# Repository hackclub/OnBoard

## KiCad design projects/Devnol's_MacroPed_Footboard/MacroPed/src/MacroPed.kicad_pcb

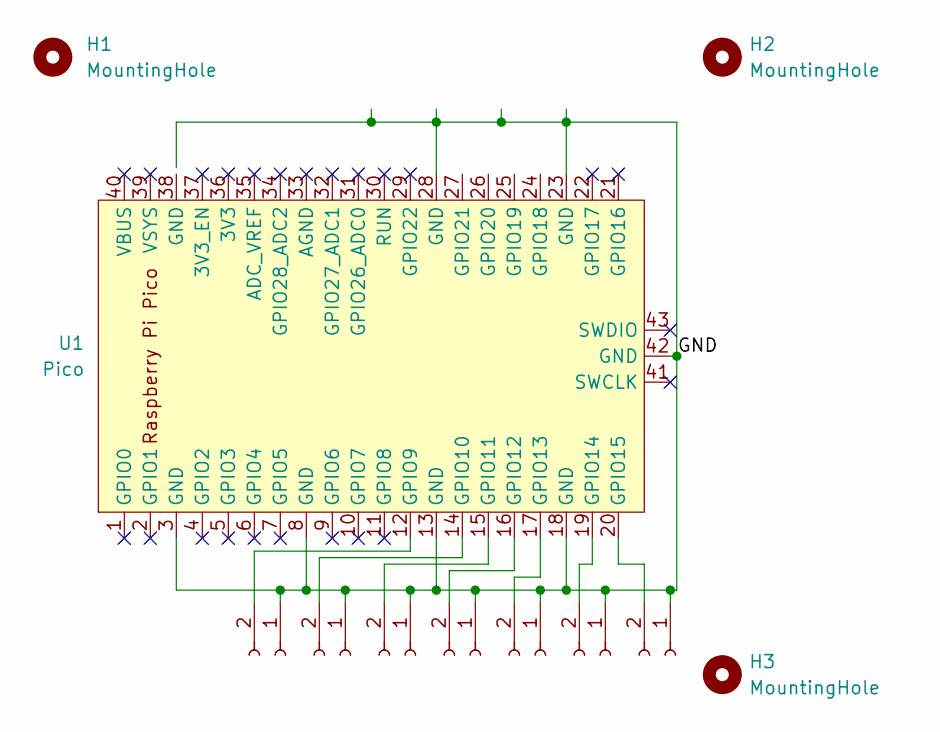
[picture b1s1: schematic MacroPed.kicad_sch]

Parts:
H1, H2, H3: MountingHole; MountingHole_2.7mm_M2.5_DIN965
J1, J2, J3, J4, J5, J6, J7: Conn_01x02_Socket; JST_PH_S2B-PH-K_1x02_P2.00mm_Horizontal
U1: Pico; RPi_Pico_SMD_TH

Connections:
/GND: J1.1, J2.1, J3.1, J4.1, J5.1, J6.1, J7.1, U1.3 (GND), U1.8 (GND), U1.13 (GND), U1.18 (GND), U1.23 (GND), U1.28 (GND), U1.42 (GND)
unnamed: J1.2, U1.12 (GPIO9)
unnamed: J2.2, U1.14 (GPIO10)
unnamed: J3.2, U1.15 (GPIO11)
unnamed: J4.2, U1.16 (GPIO12)
unnamed: J5.2, U1.17 (GPIO13)
unnamed: J6.2, U1.19 (GPIO14)
unnamed: J7.2, U1.20 (GPIO15)

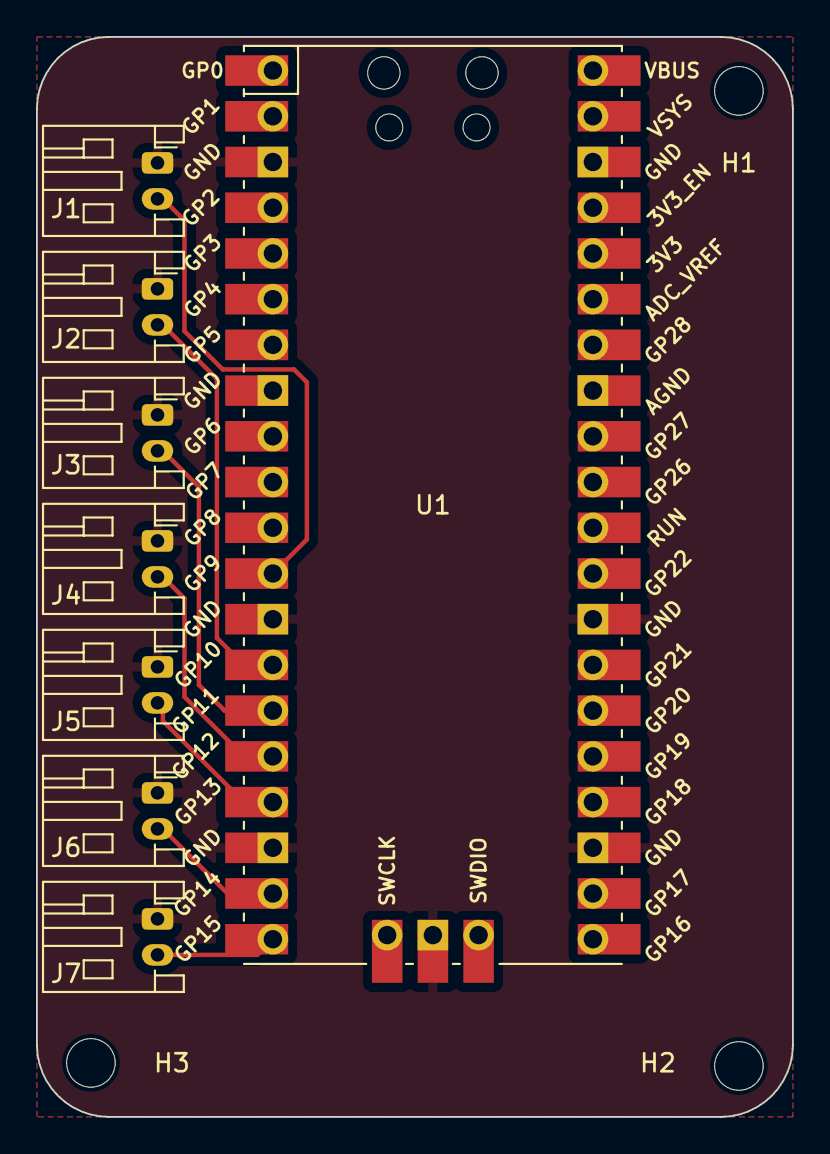
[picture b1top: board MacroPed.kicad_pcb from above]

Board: 2 copper layers, 42.0 x 60.0 mm, 11 parts (0 on the bottom side), 8 nets.

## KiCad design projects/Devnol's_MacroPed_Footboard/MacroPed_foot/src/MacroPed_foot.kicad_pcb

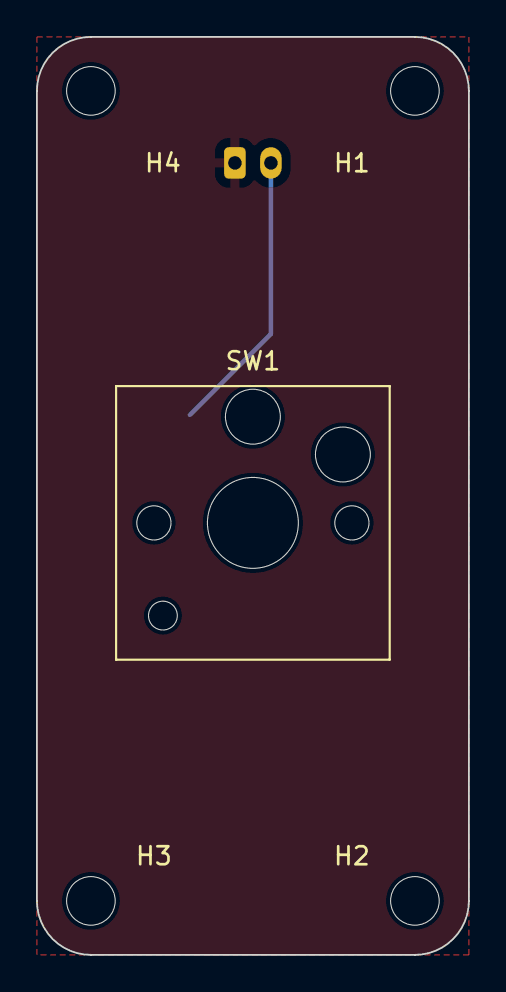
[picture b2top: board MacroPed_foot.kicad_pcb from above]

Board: 2 copper layers, 24.0 x 51.0 mm, 6 parts (1 on the bottom side), 2 nets.

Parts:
H1, H2, H3, H4: MountingHole; MountingHole_2.7mm_M2.5_DIN965
J1: Conn_01x02_Socket; JST_PH_S2B-PH-K_1x02_P2.00mm_Horizontal
SW1: SW_SPST; SW_Hotswap_Kailh_Choc_V1V2_2.00u_90deg

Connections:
/Foot_GND: J1.1, SW1.2 (B)
unnamed: J1.2, SW1.1 (A)

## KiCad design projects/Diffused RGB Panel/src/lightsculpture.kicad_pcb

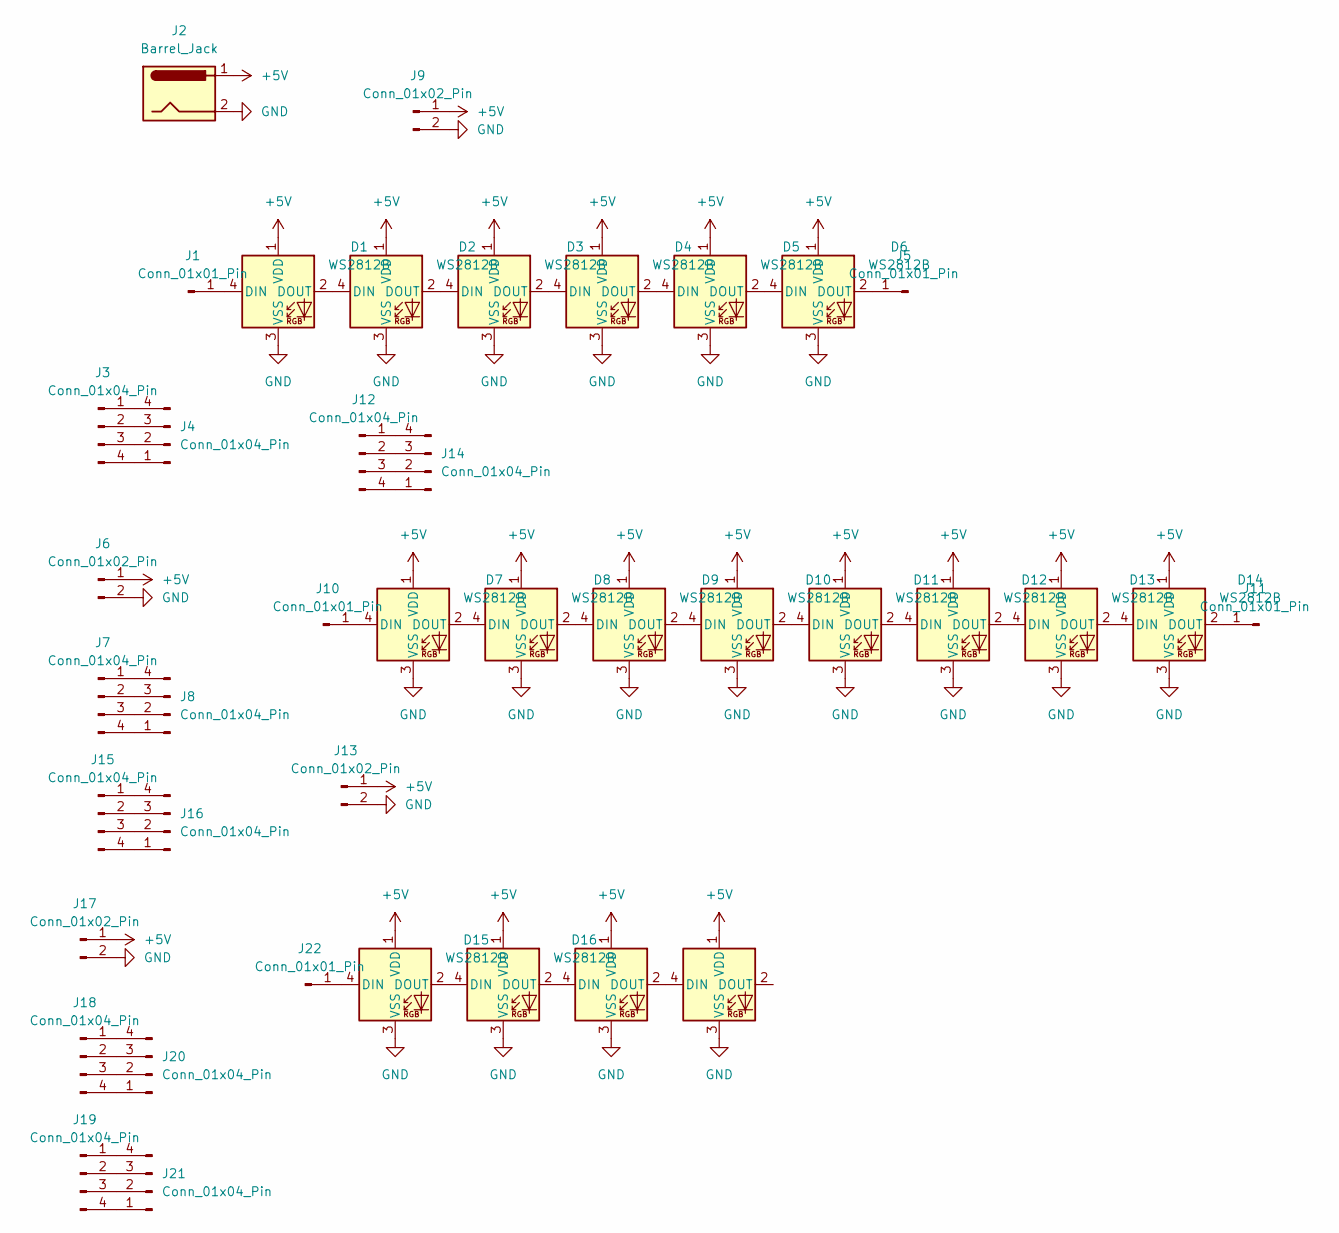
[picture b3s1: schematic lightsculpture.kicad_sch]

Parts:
D1, D2, D3, D4, D5, D6, D7, D8, D9, D10, D11, D12, D13, D14, D15, D16, D17, D18: WS2812B; LED_WS2812B_PLCC4_5.0x5.0mm_P3.2mm
J1, J5, J10, J11, J22: Conn_01x01_Pin; SolderWire-1.5sqmm_1x01_D1.7mm_OD3.9mm
J2: Barrel_Jack; SolderWire-1.5sqmm_1x02_P7.8mm_D1.7mm_OD3.9mm
J3, J4, J7, J8, J12, J14, J15, J16, J18, J19, J20, J21: Conn_01x04_Pin; SolderWire-1.5sqmm_1x04_P6mm_D1.7mm_OD3mm
J6, J9, J13, J17: Conn_01x02_Pin; SolderWire-1.5sqmm_1x02_P7.8mm_D1.7mm_OD3.9mm

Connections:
+5V: D1.1 (VDD), D2.1 (VDD), D3.1 (VDD), D4.1 (VDD), D5.1 (VDD), D6.1 (VDD), D7.1 (VDD), D8.1 (VDD), D9.1 (VDD), D10.1 (VDD), D11.1 (VDD), D12.1 (VDD), D13.1 (VDD), D14.1 (VDD), D15.1 (VDD), D16.1 (VDD), D17.1 (VDD), D18.1 (VDD), J2.1, J6.1, J9.1, J13.1, J17.1
GND: D1.3 (VSS), D2.3 (VSS), D3.3 (VSS), D4.3 (VSS), D5.3 (VSS), D6.3 (VSS), D7.3 (VSS), D8.3 (VSS), D9.3 (VSS), D10.3 (VSS), D11.3 (VSS), D12.3 (VSS), D13.3 (VSS), D14.3 (VSS), D15.3 (VSS), D16.3 (VSS), D17.3 (VSS), D18.3 (VSS), J2.2, J6.2, J9.2, J13.2, J17.2
unnamed: D1.4 (DIN), J1.1
unnamed: D1.2 (DOUT), D2.4 (DIN)
unnamed: D2.2 (DOUT), D3.4 (DIN)
unnamed: D3.2 (DOUT), D4.4 (DIN)
unnamed: D4.2 (DOUT), D5.4 (DIN)
unnamed: D5.2 (DOUT), D6.4 (DIN)
unnamed: D6.2 (DOUT), J5.1
unnamed: D7.4 (DIN), J10.1
unnamed: D7.2 (DOUT), D8.4 (DIN)
unnamed: D8.2 (DOUT), D9.4 (DIN)
unnamed: D9.2 (DOUT), D10.4 (DIN)
unnamed: D10.2 (DOUT), D11.4 (DIN)
unnamed: D11.2 (DOUT), D12.4 (DIN)
unnamed: D12.2 (DOUT), D13.4 (DIN)
unnamed: D13.2 (DOUT), D14.4 (DIN)
unnamed: D14.2 (DOUT), J11.1
unnamed: D15.4 (DIN), J22.1
unnamed: D15.2 (DOUT), D16.4 (DIN)
unnamed: D16.2 (DOUT), D17.4 (DIN)
unnamed: D17.2 (DOUT), D18.4 (DIN)
unnamed: J3.1, J4.4
unnamed: J3.2, J4.3
unnamed: J3.3, J4.2
unnamed: J3.4, J4.1
unnamed: J7.1, J8.4
unnamed: J7.2, J8.3
unnamed: J7.3, J8.2
unnamed: J7.4, J8.1
unnamed: J12.1, J14.4
unnamed: J12.2, J14.3
unnamed: J12.3, J14.2
unnamed: J12.4, J14.1
unnamed: J15.1, J16.4
unnamed: J15.2, J16.3
unnamed: J15.3, J16.2
unnamed: J15.4, J16.1
unnamed: J18.1, J20.4
unnamed: J18.2, J20.3
unnamed: J18.3, J20.2
unnamed: J18.4, J20.1
unnamed: J19.1, J21.4
unnamed: J19.2, J21.3
unnamed: J19.3, J21.2
unnamed: J19.4, J21.1

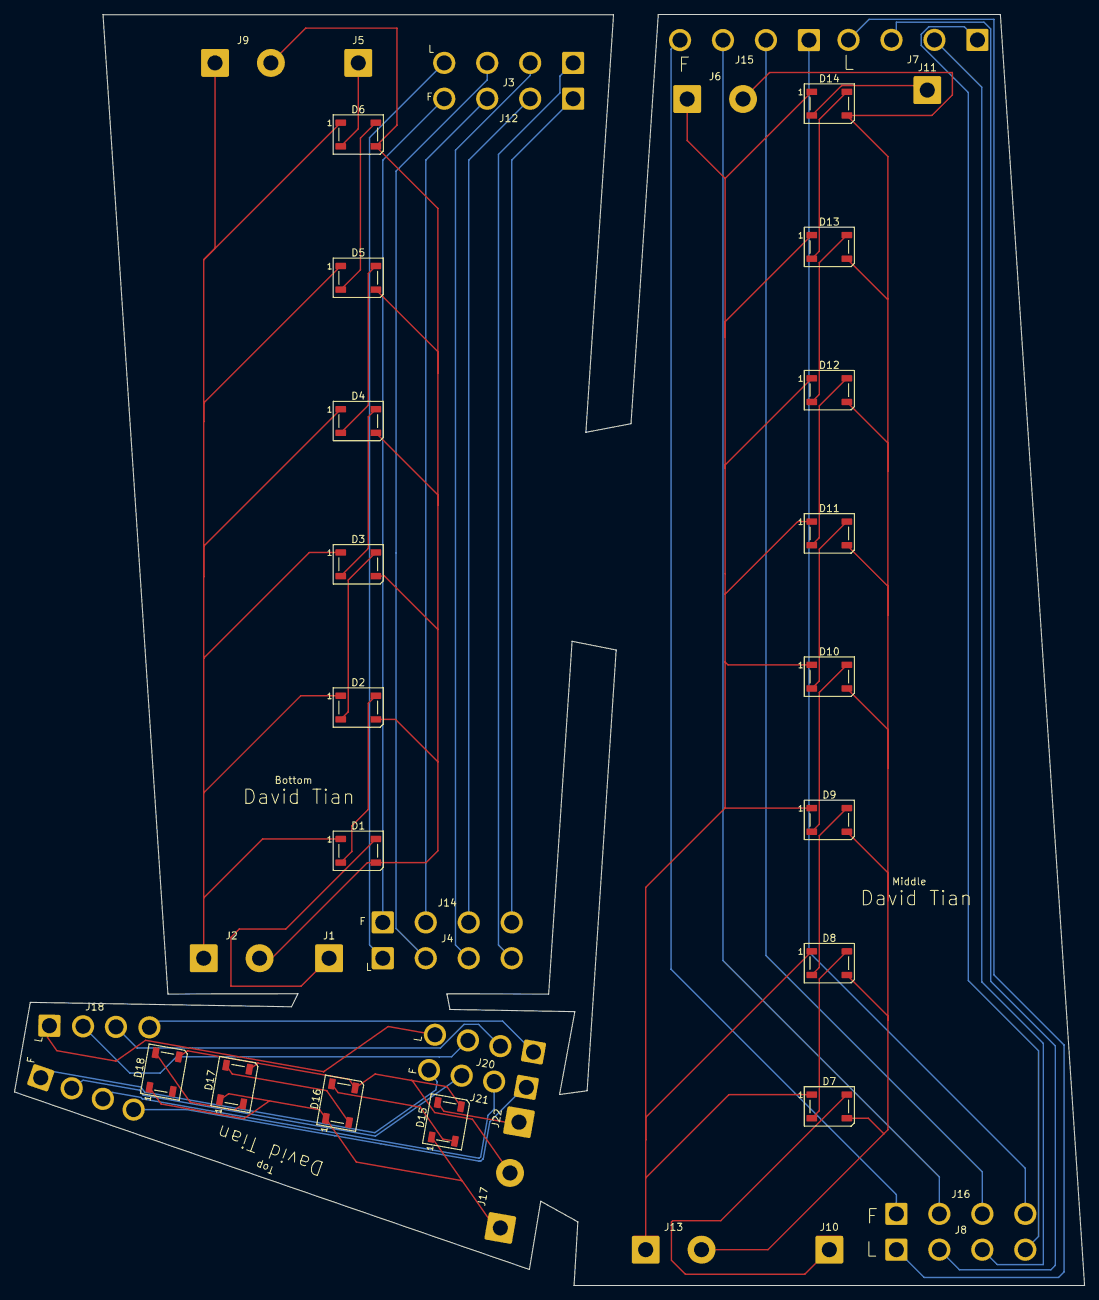
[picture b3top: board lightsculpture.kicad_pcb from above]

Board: 2 copper layers, 149.4 x 177.4 mm, 40 parts (1 on the bottom side), 46 nets.

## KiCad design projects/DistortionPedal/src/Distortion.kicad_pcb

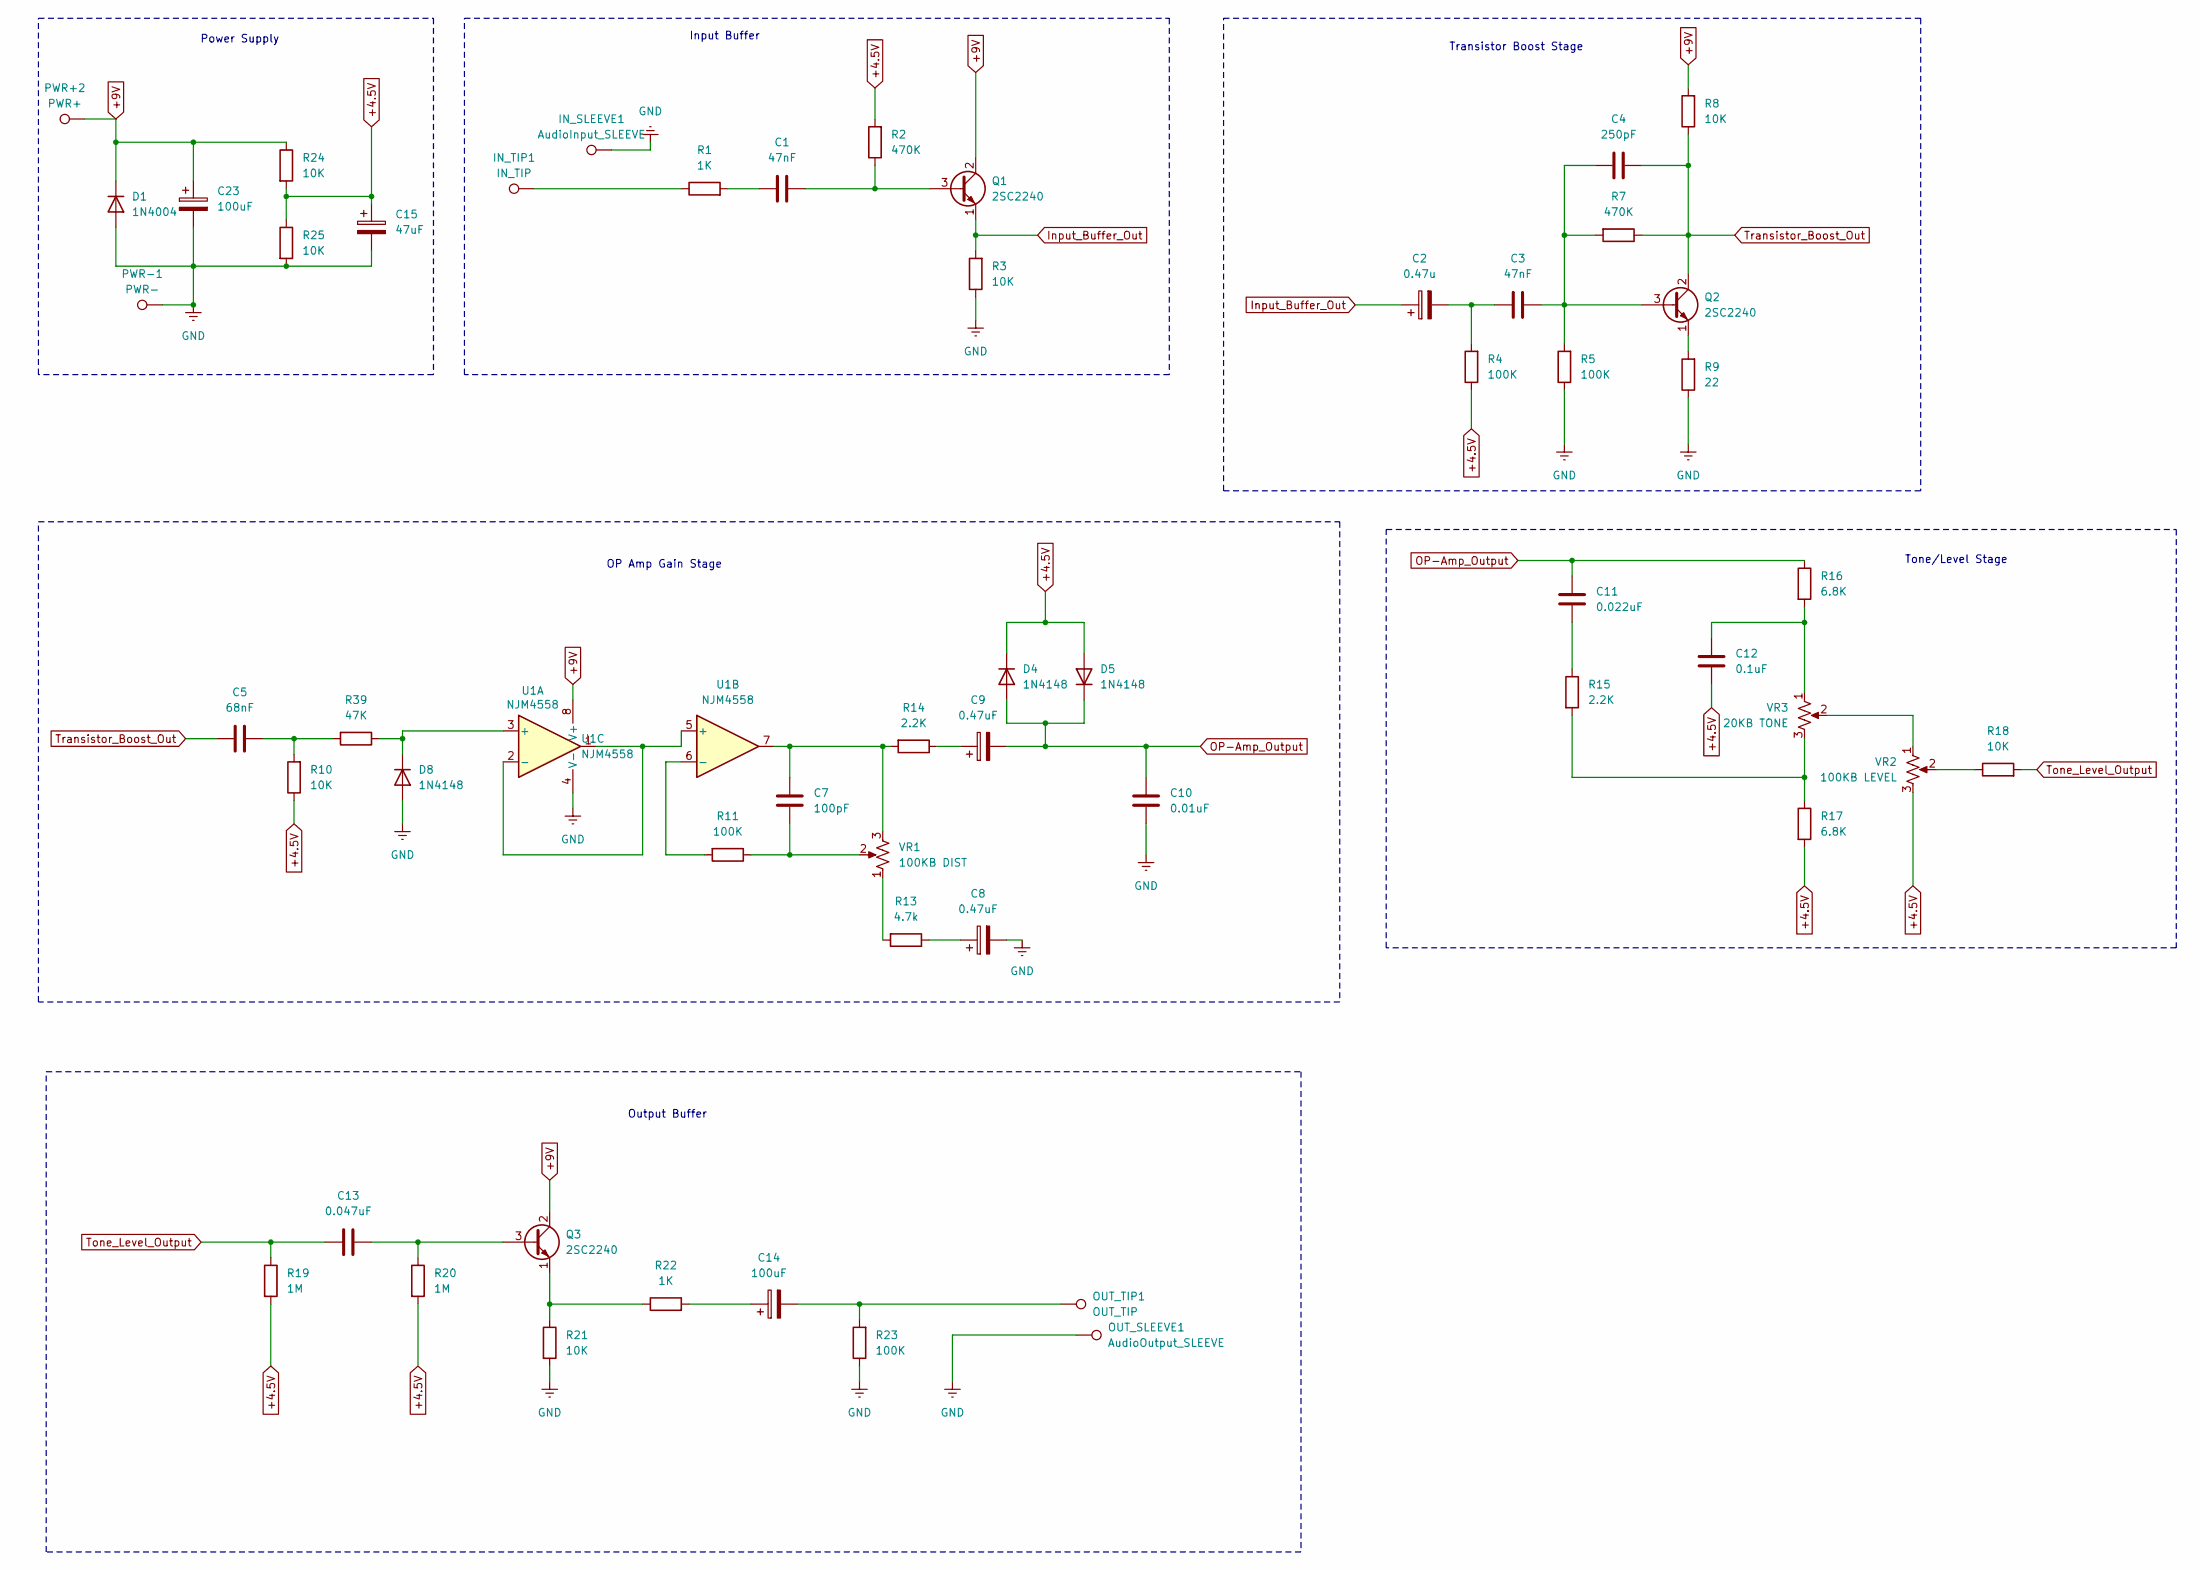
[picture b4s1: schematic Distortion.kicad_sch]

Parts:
C1, C3: 47nF; C_Disc_D5.0mm_W2.5mm_P2.50mm
C2: 0.47u; CP_Radial_D5.0mm_P2.50mm
C4: 250pF; C_Disc_D5.0mm_W2.5mm_P2.50mm
C5: 68nF; C_Disc_D5.0mm_W2.5mm_P2.50mm
C7: 100pF; C_Disc_D5.0mm_W2.5mm_P2.50mm
C8, C9: 0.47uF; CP_Radial_D5.0mm_P2.50mm
C10: 0.01uF; C_Disc_D5.0mm_W2.5mm_P2.50mm
C11: 0.022uF; C_Disc_D5.0mm_W2.5mm_P2.50mm
C12: 0.1uF; C_Disc_D5.0mm_W2.5mm_P2.50mm
C13: 0.047uF; C_Disc_D5.0mm_W2.5mm_P2.50mm
C14, C23: 100uF; CP_Radial_D5.0mm_P2.50mm
C15: 47uF; CP_Radial_D5.0mm_P2.50mm
D1: 1N4004; D_DO-35_SOD27_P7.62mm_Horizontal
D4, D5, D8: 1N4148; D_DO-35_SOD27_P7.62mm_Horizontal
IN_SLEEVE1: AudioInput_SLEEVE; TestPoint_THTPad_2.5x2.5mm_Drill1.2mm
IN_TIP1: IN_TIP; TestPoint_THTPad_2.5x2.5mm_Drill1.2mm
OUT_SLEEVE1: AudioOutput_SLEEVE; TestPoint_THTPad_2.5x2.5mm_Drill1.2mm
OUT_TIP1: OUT_TIP; TestPoint_THTPad_2.5x2.5mm_Drill1.2mm
PWR+2: PWR+; TestPoint_THTPad_2.5x2.5mm_Drill1.2mm
PWR-1: PWR-; TestPoint_THTPad_2.5x2.5mm_Drill1.2mm
Q1, Q2, Q3: 2SC2240; TO-92_Inline
R1, R22: 1K; R_Axial_DIN0207_L6.3mm_D2.5mm_P10.16mm_Horizontal
R2, R7: 470K; R_Axial_DIN0207_L6.3mm_D2.5mm_P10.16mm_Horizontal
R3, R8, R10, R18, R21, R24, R25: 10K; R_Axial_DIN0207_L6.3mm_D2.5mm_P10.16mm_Horizontal
R4, R5, R11, R23: 100K; R_Axial_DIN0207_L6.3mm_D2.5mm_P10.16mm_Horizontal
R9: 22; R_Axial_DIN0207_L6.3mm_D2.5mm_P10.16mm_Horizontal
R13: 4.7k; R_Axial_DIN0207_L6.3mm_D2.5mm_P10.16mm_Horizontal
R14, R15: 2.2K; R_Axial_DIN0207_L6.3mm_D2.5mm_P10.16mm_Horizontal
R16, R17: 6.8K; R_Axial_DIN0207_L6.3mm_D2.5mm_P10.16mm_Horizontal
R19, R20: 1M; R_Axial_DIN0207_L6.3mm_D2.5mm_P10.16mm_Horizontal
R39: 47K; R_Axial_DIN0207_L6.3mm_D2.5mm_P10.16mm_Horizontal
U1: NJM4558; SIP-8_19x3mm_P2.54mm
VR1: 100KB DIST; POT
VR2: 100KB LEVEL; POT
VR3: 20KB TONE; POT

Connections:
+4.5V: C12.1, C15.1, D4.1 (K), D5.2 (A), R2.2, R4.1, R10.1, R17.2, R19.2, R20.2, R24.2, R25.1, VR2.3
+9V: C23.1, D1.1 (K), PWR+2.1, Q1.2 (C), Q3.2 (C), R8.2, R24.1, U1.8 (V+)
GND: C8.2, C10.1, C15.2, C23.2, D1.2 (A), D8.2 (A), IN_SLEEVE1.1, OUT_SLEEVE1.1, PWR-1.1, R3.1, R5.1, R9.1, R21.2, R23.1, R25.2, U1.4 (V-)
Input_Buffer_Out: C2.1, Q1.1 (E), R3.2
unnamed: C1.1, R1.2
unnamed: C2.2, C3.1, R4.2
unnamed: C5.2, R10.2, R39.2
unnamed: C7.1, R11.1, VR1.2
unnamed: C7.2, R14.2, U1.7, VR1.3
unnamed: C8.1, R13.1
unnamed: C9.1, R14.1
unnamed: C11.1, R15.1
unnamed: C12.2, R16.2, VR3.1
unnamed: C14.1, R22.2
unnamed: C14.2, OUT_TIP1.1, R23.2
unnamed: D8.1 (K), R39.1, U1.3 (+)
unnamed: IN_TIP1.1, R1.1
unnamed: C1.2, Q1.3 (B), R2.1
unnamed: C3.2, C4.1, Q2.3 (B), R5.2, R7.2
unnamed: Q2.1 (E), R9.2
unnamed: C13.1, Q3.3 (B), R20.1
unnamed: Q3.1 (E), R21.1, R22.1
unnamed: R13.2, VR1.1
unnamed: R15.2, R17.1, VR3.3
unnamed: R18.1, VR2.2
unnamed: U1.1, U1.2 (-), U1.5 (+)
unnamed: R11.2, U1.6 (-)
unnamed: VR2.1, VR3.2
OP-Amp_Output: C9.2, C10.2, C11.2, D4.2 (A), D5.1 (K), R16.1
Tone_Level_Output: C13.2, R18.2, R19.1
Transistor_Boost_Out: C4.2, C5.1, Q2.2 (C), R7.1, R8.1

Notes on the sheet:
Transistor Boost Stage
Tone/Level Stage
Input Buffer
OP Amp Gain Stage
Power Supply
Output Buffer

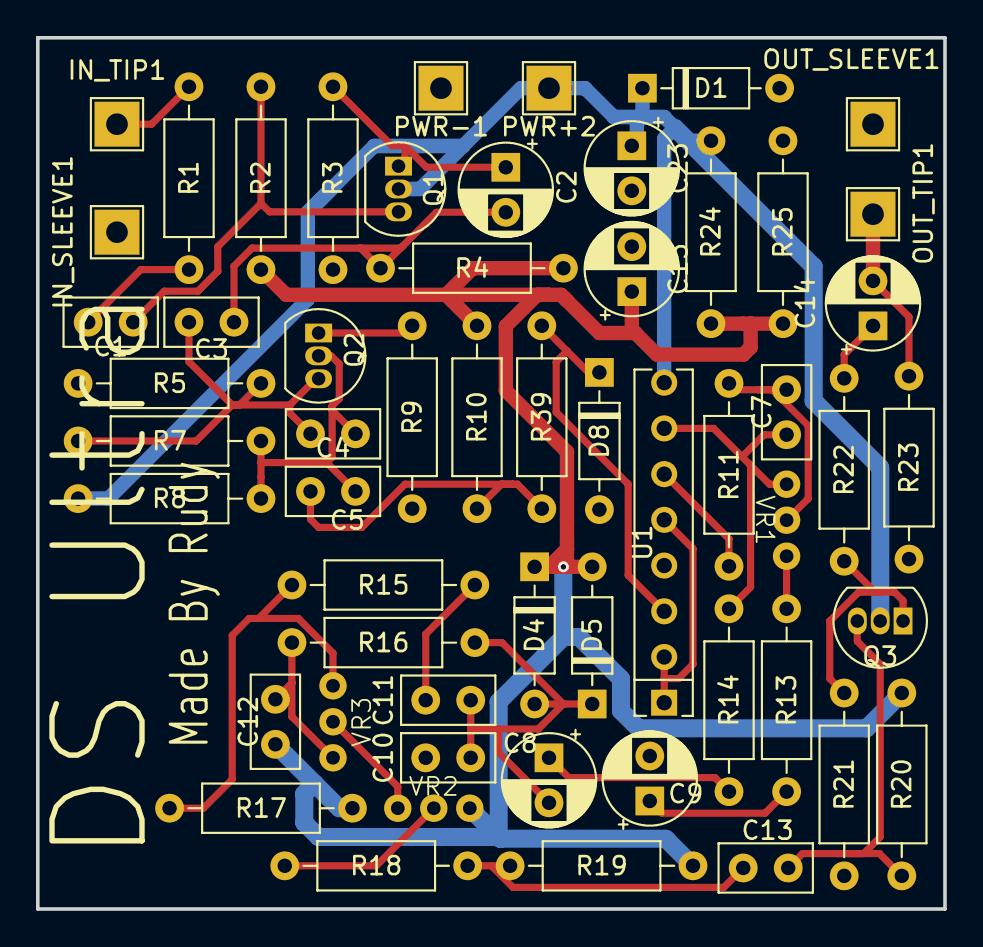
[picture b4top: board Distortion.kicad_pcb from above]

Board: 2 copper layers, 50.4 x 48.4 mm, 56 parts (0 on the bottom side), 31 nets.
